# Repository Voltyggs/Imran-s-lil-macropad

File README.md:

# Imran-s-lil-macropad

Hiya! 
i'm Imran Ahmed, and this is my Hack/MacroPad submission for the blueprint program

here, I made a macropad with the SEEED XIAO RP3040 DIP as the microcontroller, 2 MINI-LEDs, 7 Cherry MX switches n keycaps, and a EC11 rotary encoder switch.

Here, you can see the general view of the macropad:

I tried to keep everything minimal and simple, and I think i achieved it pretty well

Here's the schematic:

and the final look:

for the project, you'll need: <br />
<br />
1x SEEED XIAO RP2040-DIP <br />
1x EC11 Rotary encoder switch <br />
4x M3x16mm screws <br />
2x SK6812 MINI-E LEDs <br />
7x cherry MX swwitches <br />
7x keycaps for the Cherry MX switches <br />

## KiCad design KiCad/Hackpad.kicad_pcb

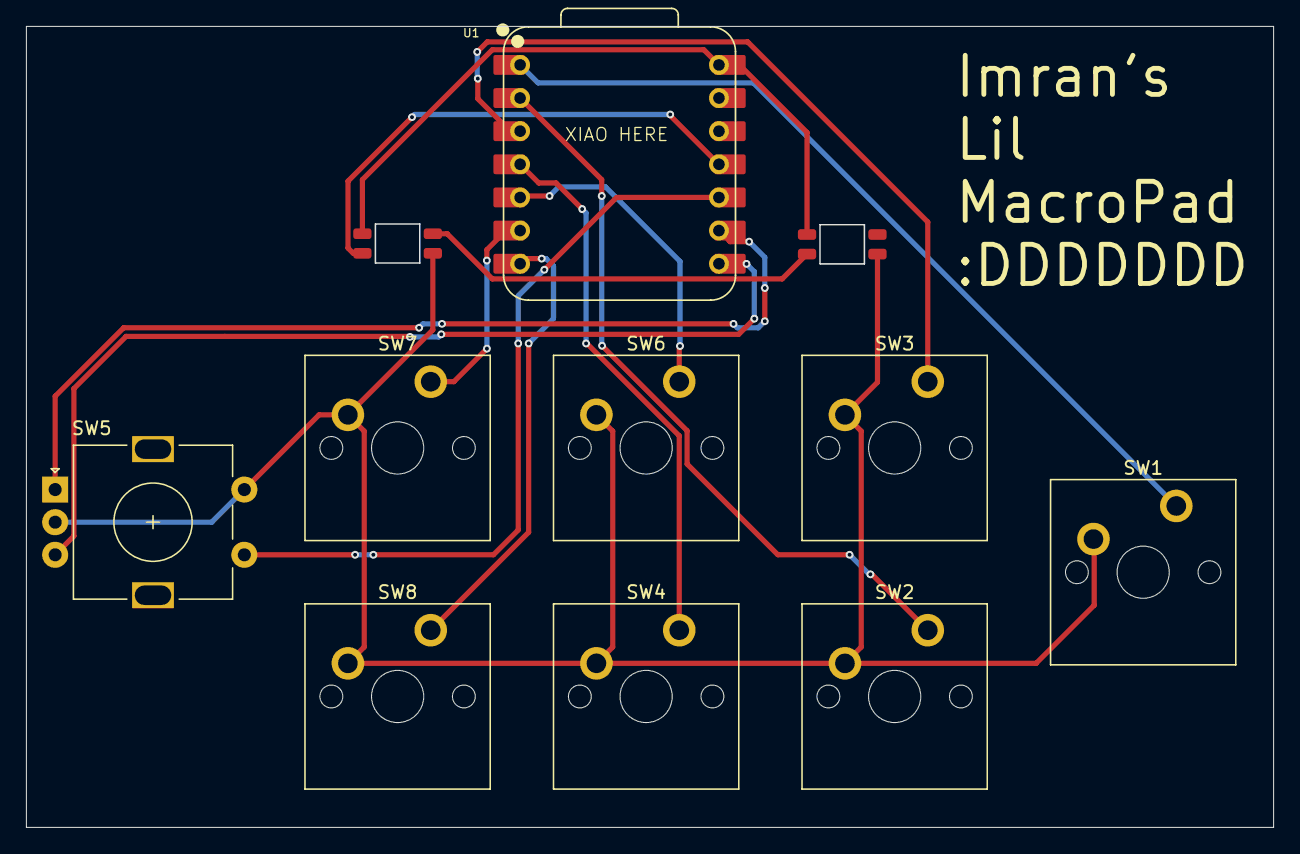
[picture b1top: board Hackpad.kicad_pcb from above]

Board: 2 copper layers, 95.5 x 61.3 mm, 11 parts (0 on the bottom side), 14 nets.

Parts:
D1, D2: SK6812MINI; LED_SK6812MINI
SW1, SW2, SW3, SW4, SW6, SW7, SW8: SW_Push; MX_PCB_1.00u
SW5: RotaryEncoder_Switch; RotaryEncoder_Alps_EC11E-Switch_Vertical_H20mm
U1: XIAO-RP2040-DIP

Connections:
+5V: D1.4 (VDD), D2.4 (VDD), U1.14 (VBUS)
GND: D1.2 (VSS), D2.2 (VSS), SW1.1, SW2.1, SW3.1, SW4.1, SW5.C, SW5.S2, SW6.1, SW7.1, SW8.1, U1.13 (GND)
unnamed: D1.3 (DIN), U1.11 (GPIO3/MOSI)
unnamed: D1.1 (DOUT), D2.3 (DIN)
unnamed: SW8.2, U1.7 (GPIO0/TX)
unnamed: SW5.B, U1.8 (GPIO1/RX)
unnamed: SW5.A, U1.9 (GPIO2/SCK)
unnamed: SW5.S1, U1.10 (GPIO4/MISO)
unnamed: SW6.2, U1.5 (GPIO6/SDA)
unnamed: SW7.2, U1.6 (GPIO7/SCL)
unnamed: SW1.2, U1.1 (GPIO26/ADC0/A0)
unnamed: SW2.2, U1.2 (GPIO27/ADC1/A1)
unnamed: SW3.2, U1.3 (GPIO28/ADC2/A2)
unnamed: SW4.2, U1.4 (GPIO29/ADC3/A3)

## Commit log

2025-12-05 Create CAD or Fusion 360
2025-12-05 Create temp
2025-12-05 Add image placeholder to README
2025-12-05 Update image in README with proper HTML tag
2025-12-05 Update README with project description and images
    Added project details, images, and component list.
2025-12-05 Update README with macropad project information
    Added images and project details for the macropad.
2025-12-05 Update README with schematic and parts list
    Fixed formatting and added missing components in the parts list.
2025-12-05 Update README with project hardware requirements
    Added hardware requirements for the project.
2025-12-05 Fix typo in introduction of README
2025-12-05 Fix formatting for screws in README.md
